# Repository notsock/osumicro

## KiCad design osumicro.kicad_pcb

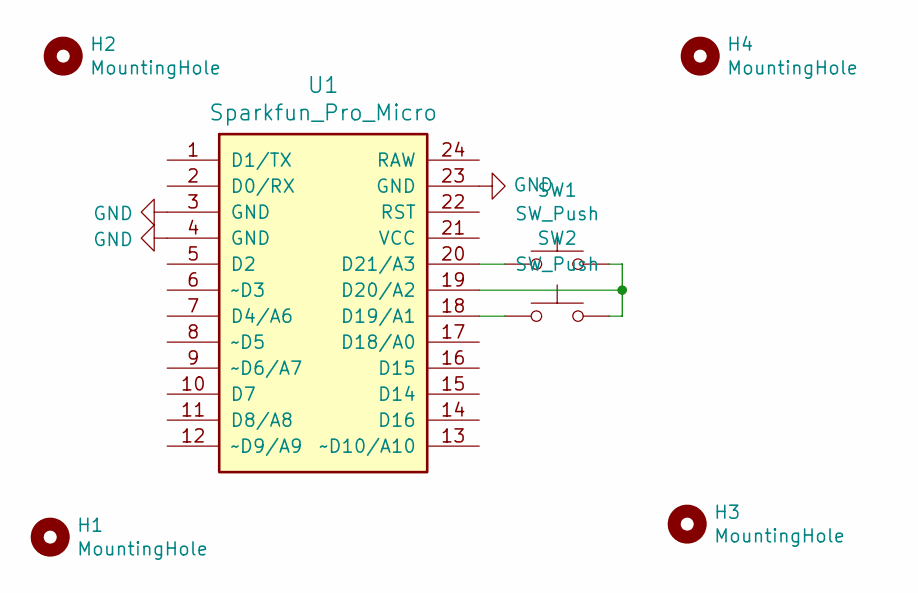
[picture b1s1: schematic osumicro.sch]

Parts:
H1, H2, H3, H4: MountingHole; MountingHole_2.2mm_M2_DIN965
SW1, SW2: SW_Push; Kailh_socket_MX_optional
U1: Sparkfun_Pro_Micro

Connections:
GND: U1.3 (GND), U1.4 (GND), U1.23 (GND)
unnamed: SW1.1, U1.20 (D21/A3)
unnamed: SW1.2, SW2.2, U1.19 (D20/A2)
unnamed: SW2.1, U1.18 (D19/A1)

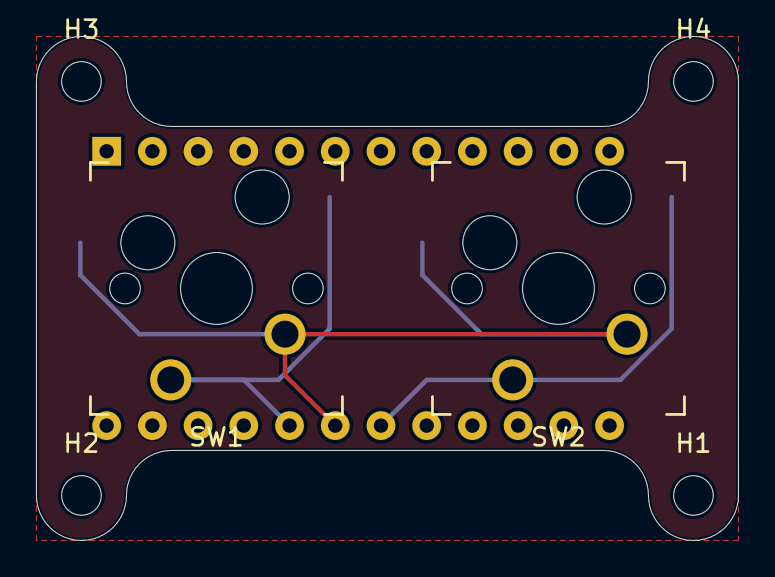
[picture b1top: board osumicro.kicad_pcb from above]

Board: 2 copper layers, 39.0 x 28.0 mm, 7 parts (1 on the bottom side), 4 nets.

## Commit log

2021-04-21 rev 1
